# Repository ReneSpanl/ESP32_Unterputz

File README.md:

# ESP32_Unterputz
A PCB to allow an ESP32 in an Underputz spacing, using this small spacing underneath a wall mount means that the tolerances are extraordinarily small. Therefor use your own brain to make it work, Modules other than the ESP32-WROOM-U do not specifically work, because the pre-mounted antenna is using too much space.

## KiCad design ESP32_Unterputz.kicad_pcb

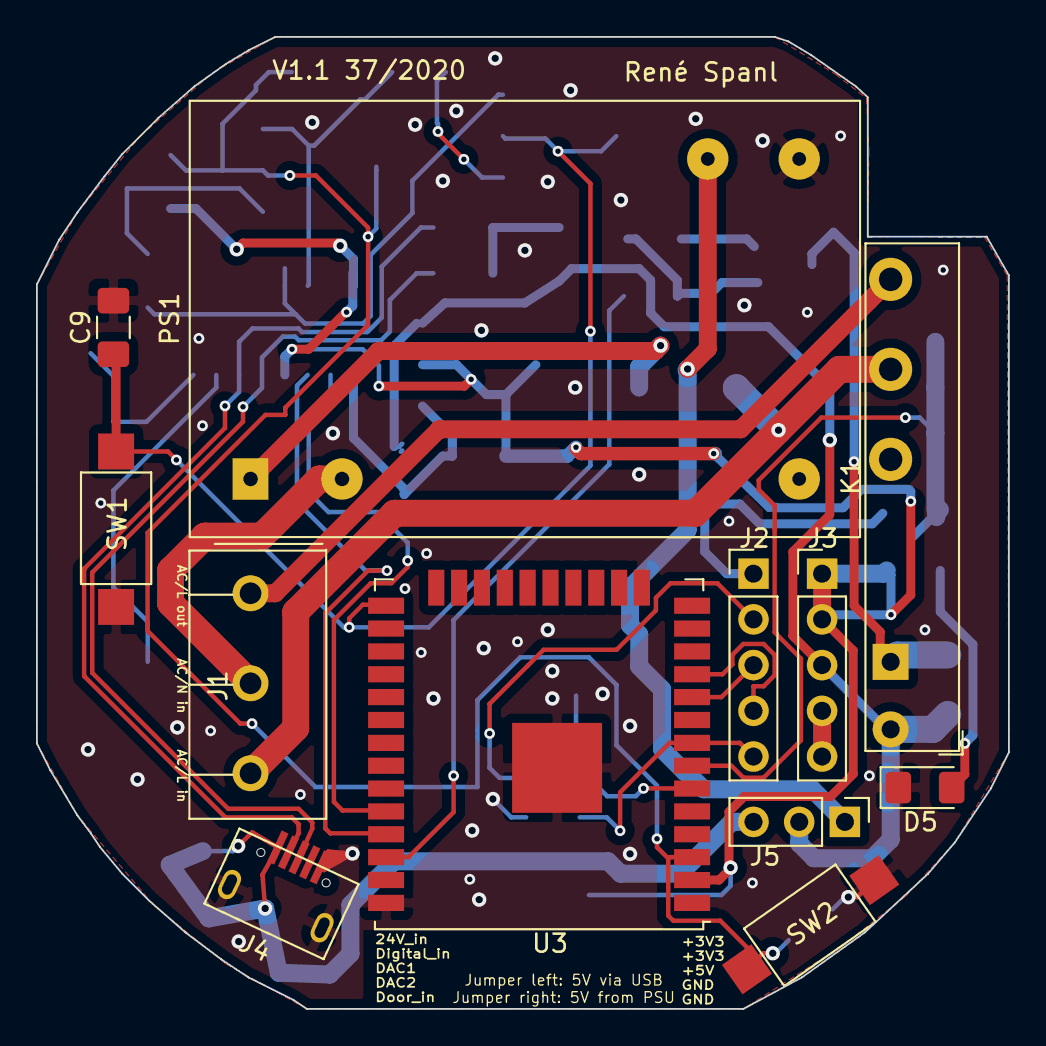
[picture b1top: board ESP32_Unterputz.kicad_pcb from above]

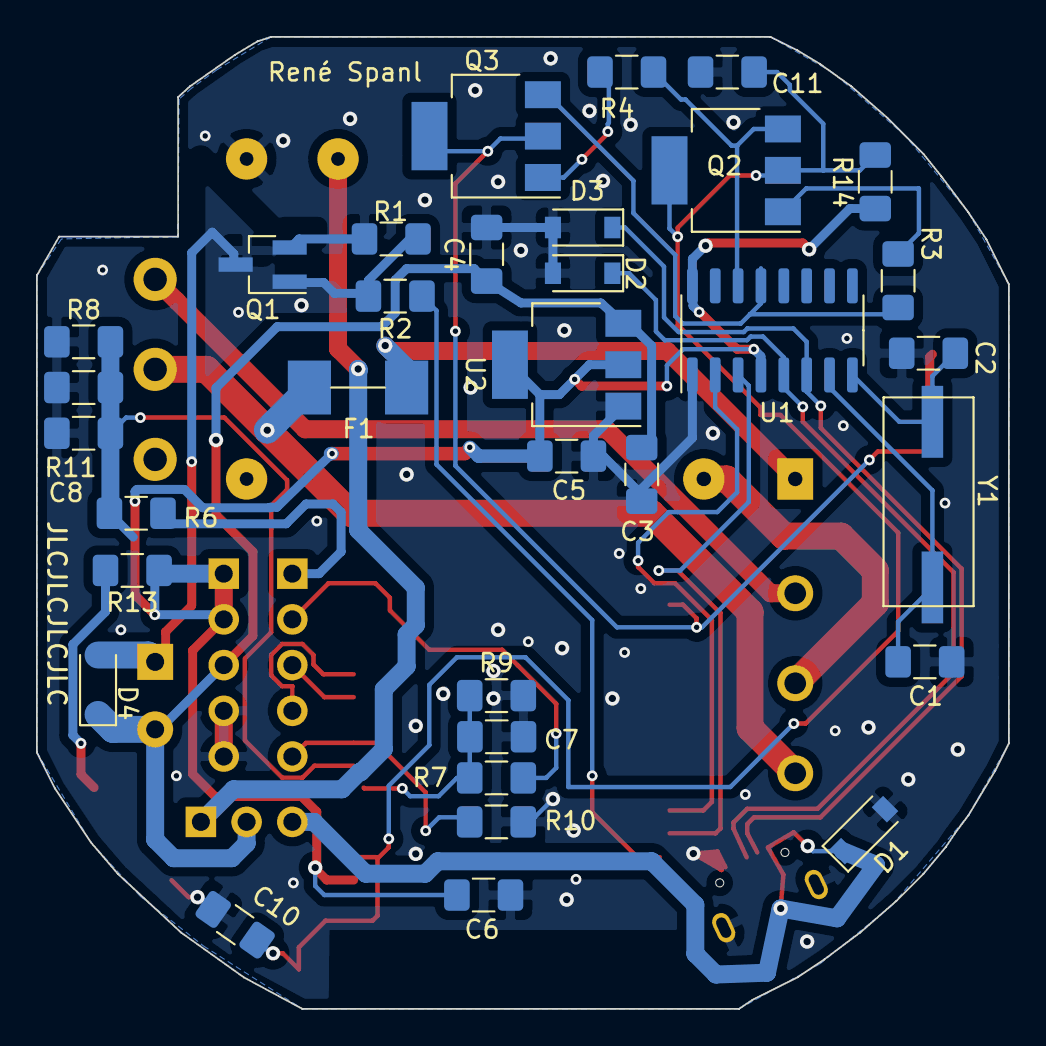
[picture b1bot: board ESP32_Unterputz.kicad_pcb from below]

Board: 2 copper layers, 54.0 x 54.0 mm, 45 parts (33 on the bottom side), 32 nets.

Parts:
C1, C2: 22p; C_1206_3216Metric_Pad1.42x1.75mm_HandSolder
C3, C6: 22uF; C_1206_3216Metric_Pad1.42x1.75mm_HandSolder
C4, C5, C7, C8, C9, C10, C11: 100n; C_1206_3216Metric_Pad1.42x1.75mm_HandSolder
D1, D2, D3, D4: SJD12C05L01; D_SOD-123
D5: LED; LED_1206_3216Metric_Pad1.42x1.75mm_HandSolder
F1: Fuse_Small; Fuse_24E0750A
J1: Screw_Terminal; TerminalBlock_DB301V-50.0-3P
J2, J3: Conn_01x05_Male; PinHeader_1x05_P2.54mm_Vertical
J4: USB_B_Micro; USB_XKB
J5: Conn_01x03_Male; PinHeader_1x03_P2.54mm_Vertical
K1: FINDER-34.51; Relay_SPDT_Finder_34.51_Vertical
PS1: IRM-03-5; Converter_ACDC_MeanWell_IRM-03-xx_THT
Q1: Si2302DS; SOT-23_Handsoldering
Q2, Q3: PZT2222A; SOT-223-3_TabPin2
R1, R3, R4, R6, R10, R14: 10k; R_1206_3216Metric_Pad1.42x1.75mm_HandSolder
R2, R7: 100; R_1206_3216Metric_Pad1.42x1.75mm_HandSolder
R8: 1800; R_1206_3216Metric_Pad1.42x1.75mm_HandSolder
R9: 150; R_1206_3216Metric_Pad1.42x1.75mm_HandSolder
R11: 6800; R_1206_3216Metric_Pad1.42x1.75mm_HandSolder
R13: 210; R_1206_3216Metric_Pad1.42x1.75mm_HandSolder
SW1, SW2: SW_DIP_x01; Switch_HYP
U1: CH340G; SOIC-16_3.9x9.9mm_P1.27mm
U2: AMS1117-3.3; SOT-223-3_TabPin2
U3: ESP32-WROOM-32U
Y1: 12 Mhz; Crystal_12Mhz

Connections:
5V_ext: D1.1, J4.1, J5.3
24V_in: J2.1, R6.2
+3V3: C5.1, C6.1, J3.1, J3.2, R13.1, R14.1, U1.4, U1.16, U2.2, U3.2
+5V: C3.1, C4.1, D4.1, J3.3, J5.2, K1.A2, U2.3
DAC1: J2.3, U3.10
DAC2: J2.4, U3.11
DIGITAL_in: J2.2, R7.2
DOOR_in: J2.5, R10.1, U3.8
EN: C10.1, C11.1, Q2.2, R14.2, SW2.2, U3.3
GND: C1.2, C2.2, C3.2, C4.2, C5.2, C6.2, C7.2, C8.2, C9.2, C10.2, C11.2, D1.2, D2.2, D3.2, D5.1, J3.4, J3.5, J4.5, J4.6, PS1.14, Q1.2, R1.2, R8.2, R9.2, R10.2, R11.2, SW1.1, SW2.1, U1.1, U2.1, U3.1, U3.15, U3.38, U3.39
GPIO0: C9.1, Q3.2, SW1.2, U3.25
GPIO22: R2.1, U3.36
GPIO34: C7.1, R7.1, R9.1, U3.6
GPIO35: C8.1, R6.1, R8.1, R11.1, U3.7
L_in: F1.2, J1.3, K1.11
L_out: J1.1, K1.14
NEUT: J1.2, PS1.3
unnamed: C1.1, U1.7, Y1.1
unnamed: C2.1, U1.8, Y1.2
unnamed: D2.1, J4.3, U1.5
unnamed: D3.1, J4.2, U1.6
unnamed: D4.2, K1.A1, Q1.3
unnamed: D5.2, R13.2
unnamed: F1.1, PS1.1
unnamed: J5.1, PS1.16
unnamed: Q1.1, R1.1, R2.2
unnamed: Q2.1, R3.1
unnamed: Q2.3, R4.2, U1.14
unnamed: Q3.1, R4.1
unnamed: Q3.3, R3.2, U1.13
RX_CH340_OUT: U1.3, U3.35
TX_CH340_OUT: U1.2, U3.34

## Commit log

2020-09-09 Revision 1.1 to Public
    First public Revision. Use with care, no warranties ever given.
2020-10-12 Add files via upload
    The plan needs to be online aswell
